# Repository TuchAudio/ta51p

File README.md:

# TuchAudio L51p
Passive crossover filter for two-way speakers

## Purpose
This is a crossover filter intended for a homebrew speaker. Design is a bit unorthodox, but the circuit itself is flexible enough for many designs.

### L51p
Name comes from the desired configuration:

- `L`oudspeaker
- `5` in. woofer
- `1` in. dome tweeter
- Powered by **`P`hilips**

### Intended drivers

- Woofer: **Philips AD5060W8**
- Tweeter: **Philips AD0140T8**

### Filter design
The _woofer_ is expected to be **directly** connected to the speaker output, as the `AD5060W8` does perform as a _nearly-**full range**_ speaker -- space for a _series coil_ (`L1`) is included on the board if so desired.

The _tweeter_ branch includes an **attenuator** as the `AD0140T8` is extremely sensitive... Being a resistor (`R2`) in series with the tweeter, total impedance is higher, thus a second resistor (`R1`) _in parallel_ with this branch is included for correction. _Since the woofer is directly connected, keeping this branch on a somewhat higher impedance (around **14.5 Ω** with suggested values) is desired to avoid amplifier overload._

The high-pass filter is a simple **first-order** one (6 dB/oct) using a **1.5 µF** capacitor (`C1`). _Actual value must be matched to the desired cutoff frequency and the tweeter network impedance._

## Specs

### Original design (with recommended drivers)

- **Power handling:** 10 W RMS
- **Crossover frequency:** 7.3 kHz
- **Tweeter attenuation:** -10.2 dB
- **Nominal impedance:** 8Ω _(somewhat lower at very high frequencies)_

### Computing alternative values

$L_1 = \frac{1}{2π·f·Z_w}$

$R_2 = Z_t·(A_t-1)$

$\frac{1}{Z_n} = \frac{1}{R_1} + \frac{1}{Z_t+R_2}$, thus: $R_1 = \frac{Z_n(R_2+Z_t)}{R_2+Z_t - Z_n}$

$C_1 = \frac{1}{2π·f·Z_n}$

where:
- **$f$:** desired crossover frequency (Hz)
- **$Z_w$:** nominal woofer impedance (Ω)
- **$Z_t$:** nominal tweeter impedance (Ω)
- **$Z_n$:** desired tweeter network impedance, _less or equal than_ $Z_t+R_2$ (Ω)
- **$A_t$:** attenuation factor (linear, e.g.: $2$ for -6 dB)

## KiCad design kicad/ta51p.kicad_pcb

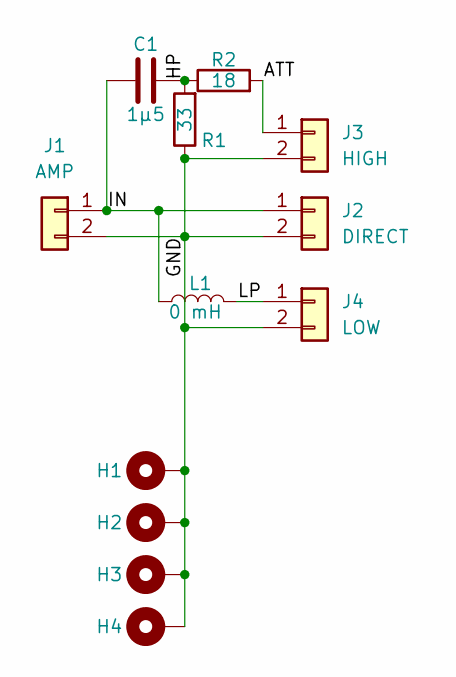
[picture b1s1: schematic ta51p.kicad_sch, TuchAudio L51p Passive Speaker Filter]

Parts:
C1: 1µ5; CP_Axial_L30.0mm_D15.0mm_P35.00mm_Horizontal
H1, H2, H3, H4: MountingHole_Pad; MountingHole_3.2mm_M3_DIN965_Pad
J1: AMP; TerminalBlock_MaiXu_MX126-5.0-02P_1x02_P5.00mm
J2: DIRECT; TerminalBlock_MaiXu_MX126-5.0-02P_1x02_P5.00mm
J3: HIGH; TerminalBlock_MaiXu_MX126-5.0-02P_1x02_P5.00mm
J4: LOW; TerminalBlock_MaiXu_MX126-5.0-02P_1x02_P5.00mm
L1: 0 mH; L_Toroid_Vertical_L28.6mm_W14.3mm_P11.43mm_Bourns_5700
R1: 33; R_Axial_DIN0617_L17.0mm_D6.0mm_P20.32mm_Horizontal
R2: 18; R_Axial_DIN0617_L17.0mm_D6.0mm_P20.32mm_Horizontal

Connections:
/ATT: J3.1, R2.2
/GND: H1.1, H2.1, H3.1, H4.1, J1.2, J2.2, J3.2, J4.2, R1.1
/HP: C1.2, R1.2, R2.1
/IN: C1.1, J1.1, J2.1, L1.1
/LP: J4.1, L1.2

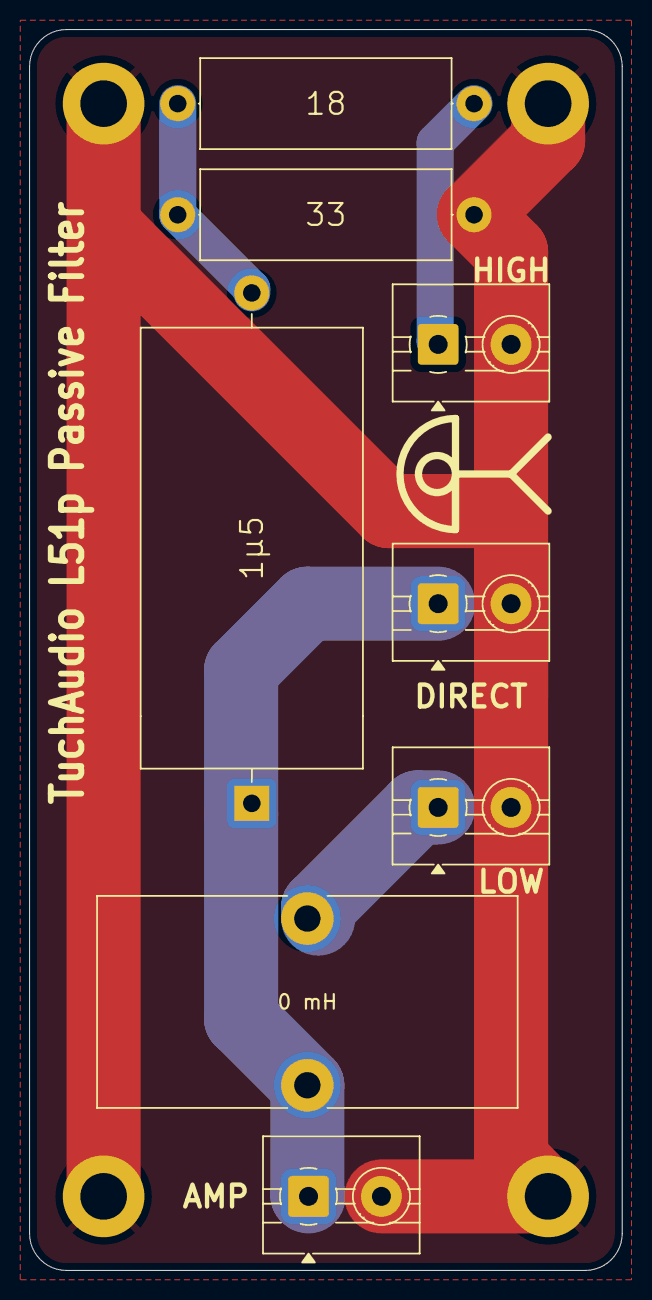
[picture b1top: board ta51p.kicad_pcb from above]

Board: 2 copper layers, 40.6 x 85.1 mm, 12 parts (0 on the bottom side), 5 nets.

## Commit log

2025-11-08 add KiCAD files
2025-11-17 Improved formulae display
2025-11-28 direct R1 computation
